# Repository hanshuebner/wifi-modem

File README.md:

# WiFi modem based on Zimodem

This project contains a PCB to turn a ESP-12F microcontroller into a
standalone WiFi modem with status LEDs and a RS-232 interface.  It is
designed to use [Zimodem](https://github.com/bozimmerman/Zimodem) as
firmware.

**Please do not use this PCB at this points.  There are bugs in it that
make it non-functional and I did not find the time to debug it yet.**

[schematics](schematic.pdf)

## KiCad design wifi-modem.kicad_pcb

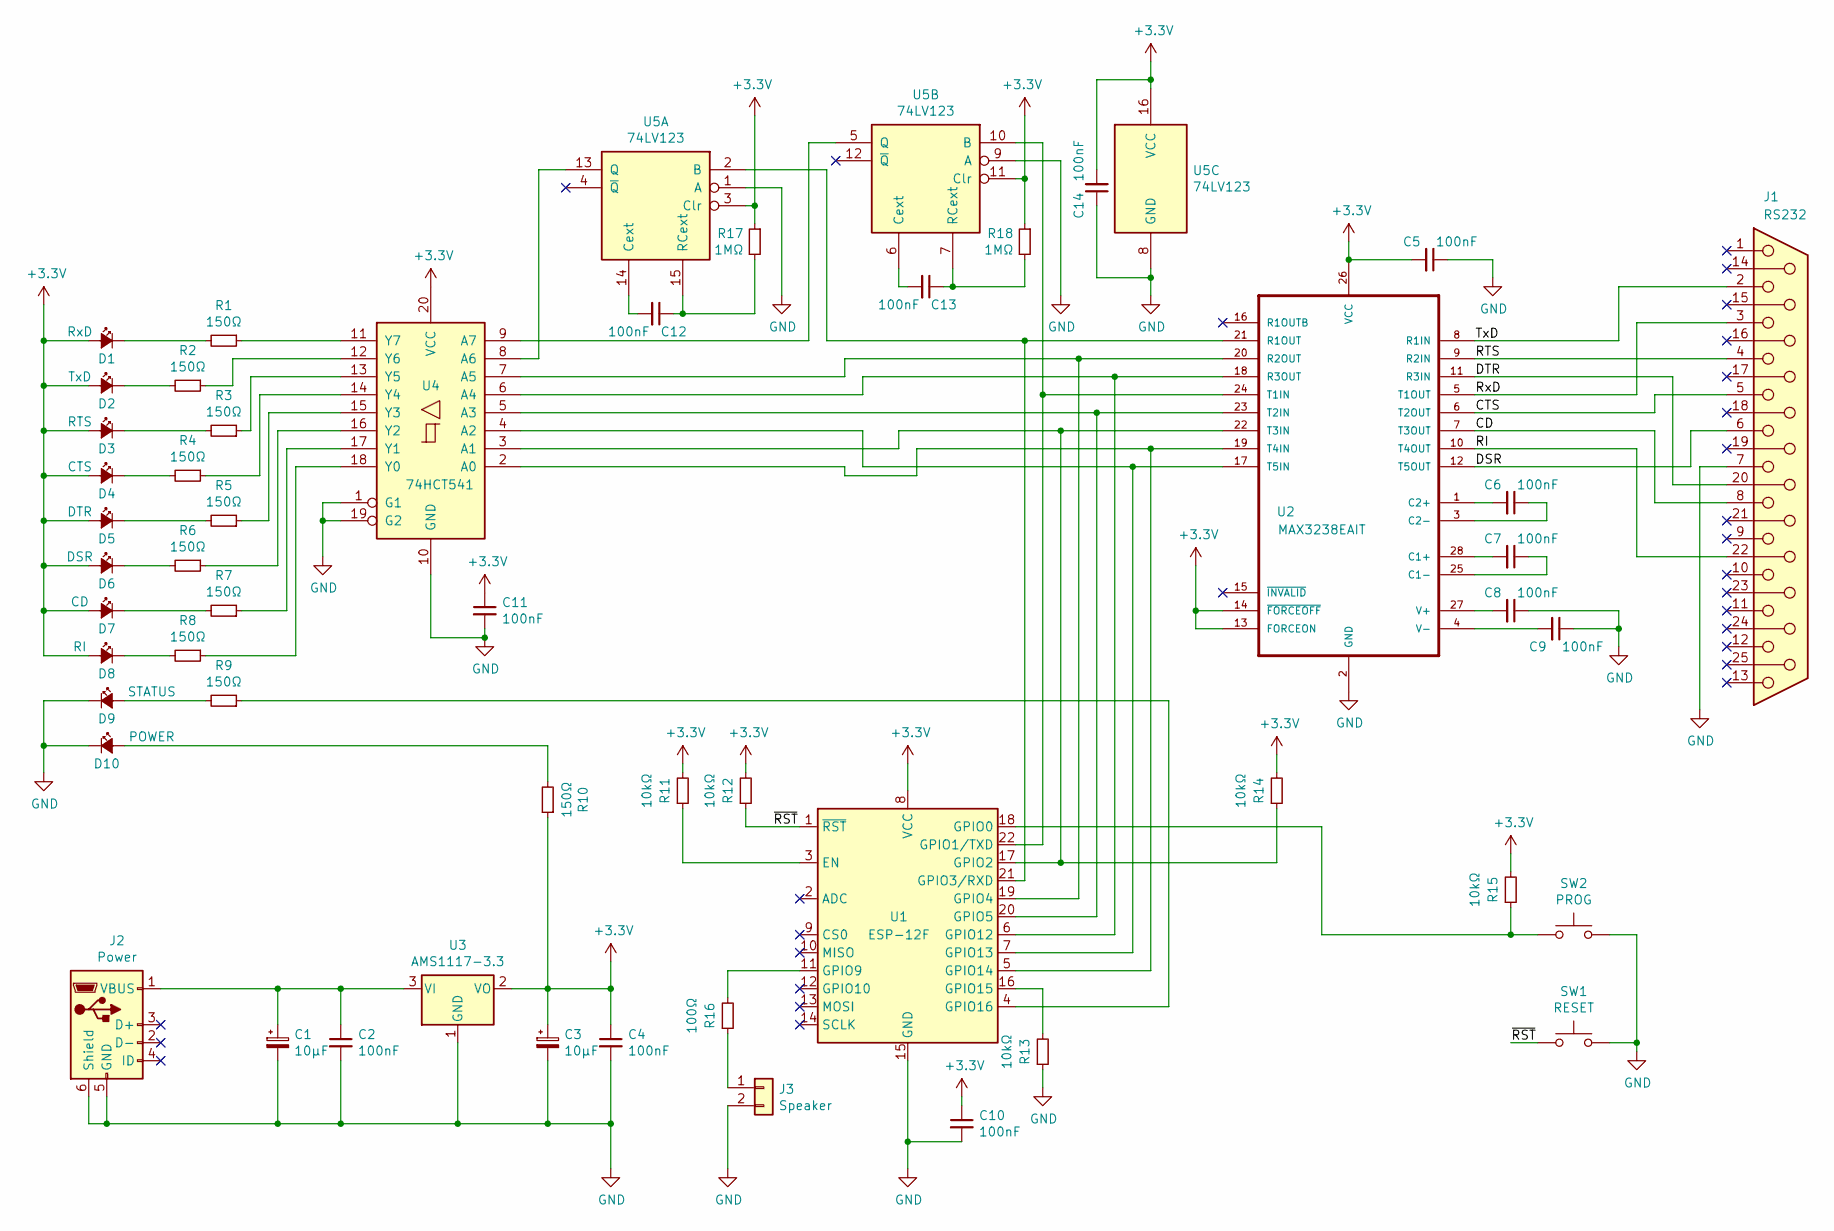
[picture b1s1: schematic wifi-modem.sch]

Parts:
C1, C3: 10µF; C_0805_2012Metric_Pad1.15x1.40mm_HandSolder
C2, C4, C5, C6, C7, C8, C9, C10, C11, C12, C13, C14: 100nF; C_0805_2012Metric_Pad1.15x1.40mm_HandSolder
D1: RxD; LED_D5.0mm
D2: TxD; LED_D5.0mm
D3: RTS; LED_D5.0mm
D4: CTS; LED_D5.0mm
D5: DTR; LED_D5.0mm
D6: DSR; LED_D5.0mm
D7: CD; LED_D5.0mm
D8: RI; LED_D5.0mm
D9: STATUS; LED_D5.0mm
D10: POWER; LED_D5.0mm
J1: RS232; DSUB-25_Female_Horizontal_P2.77x2.84mm_EdgePinOffset7.70mm_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
J2: Power; USB_Micro-B_Wuerth_629105150521
J3: Speaker; PinHeader_1x02_P2.54mm_Vertical
R1, R2, R3, R4, R5, R6, R7, R8, R9, R10: 150Ω; R_0805_2012Metric_Pad1.15x1.40mm_HandSolder
R11, R12, R13, R14, R15: 10kΩ; R_0805_2012Metric_Pad1.15x1.40mm_HandSolder
R16: 100Ω; R_0805_2012Metric_Pad1.15x1.40mm_HandSolder
R17, R18: 1MΩ; R_0805_2012Metric_Pad1.15x1.40mm_HandSolder
SW1: RESET; SW_Push_1P1T_NO_6x6mm_H9.5mm
SW2: PROG; SW_Push_1P1T_NO_6x6mm_H9.5mm
U1: ESP-12F; ESP-12E
U2: MAX3238EAIT; SOP65P777X199-28N
U3: AMS1117-3.3; SOT-223-3_TabPin2
U4: 74HCT541; TSSOP-20_4.4x6.5mm_P0.65mm
U5: 74LV123; TSSOP-16_4.4x5mm_P0.65mm

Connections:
+3V3: C3.1, C4.1, C5.2, C10.1, C11.1, C14.2, D1.2 (A), D2.2 (A), D3.2 (A), D4.2 (A), D5.2 (A), D6.2 (A), D7.2 (A), D8.2 (A), R10.1, R11.2, R12.2, R14.2, R15.2, R17.1, R18.1, U1.8 (VCC), U2.13 (FORCEON), U2.14 (~FORCEOFF~), U2.26 (VCC), U3.2 (VO), U4.20 (VCC), U5.3 (Clr), U5.11 (Clr), U5.16 (VCC)
/CD: J1.8, U2.7 (T3OUT)
/CTS: J1.5, U2.6 (T2OUT)
/DSR: J1.6, U2.12 (T5OUT)
/DTR: J1.20, U2.11 (R3IN)
/RI: J1.22, U2.10 (T4OUT)
/RTS: J1.4, U2.9 (R2IN)
/RxD: J1.3, U2.5 (T1OUT)
/TxD: J1.2, U2.8 (R1IN)
/~RST: R12.1, SW1.1, U1.1 (~RST)
GND: C1.2, C2.2, C3.2, C4.2, C5.1, C8.1, C9.1, C10.2, C11.2, C14.1, D9.1 (K), D10.1 (K), J1.7, J2.5 (GND), J2.6 (Shield), J3.2, R13.1, SW1.2, SW2.2, U1.15 (GND), U2.2 (GND), U3.1 (GND), U4.1 (G1), U4.10 (GND), U4.19 (G2), U5.1 (A), U5.8 (GND), U5.9 (A)
unnamed: C1.1, C2.1, J2.1 (VBUS), U3.3 (VI)
unnamed: C6.1, U2.3 (C2-)
unnamed: C6.2, U2.1 (C2+)
unnamed: C7.1, U2.25 (C1-)
unnamed: C7.2, U2.28 (C1+)
unnamed: C8.2, U2.27 (V+)
unnamed: C9.2, U2.4 (V-)
unnamed: C12.1, R17.2, U5.15 (RCext)
unnamed: C12.2, U5.14 (Cext)
unnamed: C13.1, R18.2, U5.7 (RCext)
unnamed: C13.2, U5.6 (Cext)
unnamed: D1.1 (K), R1.2
unnamed: D2.1 (K), R2.2
unnamed: D3.1 (K), R3.2
unnamed: D4.1 (K), R4.2
unnamed: D5.1 (K), R5.2
unnamed: D6.1 (K), R6.2
unnamed: D7.1 (K), R7.2
unnamed: D8.1 (K), R8.2
unnamed: D9.2 (A), R9.2
unnamed: D10.2 (A), R10.2
unnamed: J3.1, R16.1
unnamed: R1.1, U4.11 (Y7)
unnamed: R2.1, U4.12 (Y6)
unnamed: R3.1, U4.13 (Y5)
unnamed: R4.1, U4.14 (Y4)
unnamed: R5.1, U4.15 (Y3)
unnamed: R6.1, U4.16 (Y2)
unnamed: R7.1, U4.17 (Y1)
unnamed: R8.1, U4.18 (Y0)
unnamed: R9.1, U1.4 (GPIO16)
unnamed: R11.1, U1.3 (EN)
unnamed: R13.2, U1.16 (GPIO15)
unnamed: R14.1, U1.17 (GPIO2), U2.22 (T3IN), U4.3 (A1)
unnamed: R15.1, SW2.1, U1.18 (GPIO0)
unnamed: R16.2, U1.11 (GPIO9)
unnamed: U1.5 (GPIO14), U2.19 (T4IN), U4.2 (A0)
unnamed: U1.6 (GPIO12), U2.18 (R3OUT), U4.6 (A4)
unnamed: U1.7 (GPIO13), U2.17 (T5IN), U4.4 (A2)
unnamed: U1.19 (GPIO4), U2.20 (R2OUT), U4.7 (A5)
unnamed: U1.20 (GPIO5), U2.23 (T2IN), U4.5 (A3)
unnamed: U1.21 (GPIO3/RXD), U2.21 (R1OUT), U5.2 (B)
unnamed: U1.22 (GPIO1/TXD), U2.24 (T1IN), U5.10 (B)
unnamed: U4.8 (A6), U5.13 (Q)
unnamed: U4.9 (A7), U5.5 (Q)

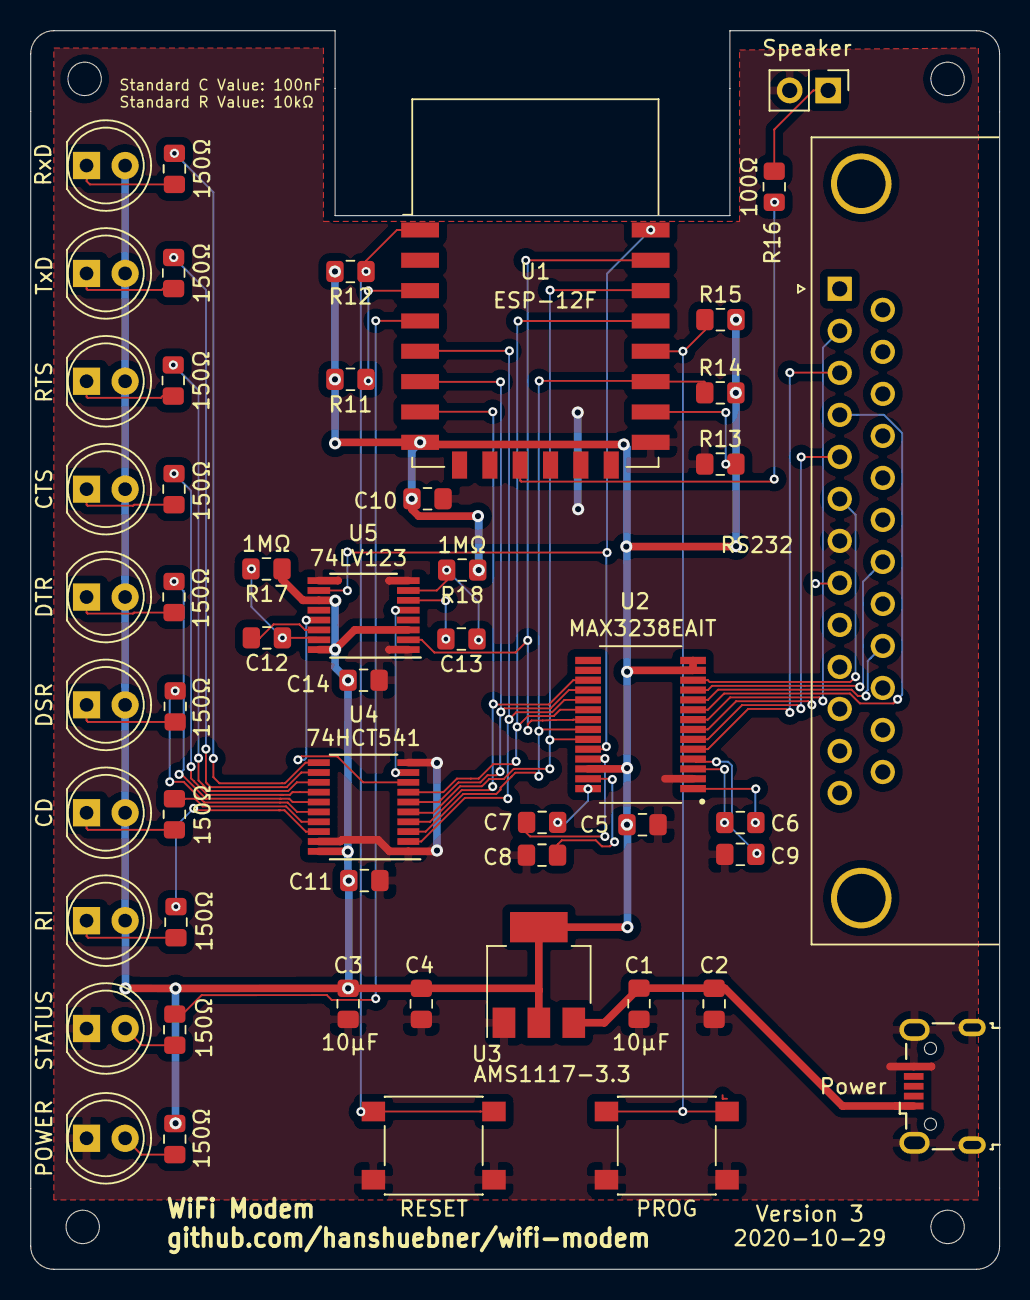
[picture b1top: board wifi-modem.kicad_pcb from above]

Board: 2 copper layers, 63.9 x 81.7 mm, 52 parts (0 on the bottom side), 56 nets.

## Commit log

2020-08-28 Snapshot
2020-08-28 Checkpoint
2020-08-28 Layout redone
2020-08-28 Fixed connectors, added Speaker, made larger
2020-08-28 Fix swapped RX/TX lines
2020-08-28 V1 sent to JLCPCB
2020-08-28 Sent to JLCPCB
2020-08-28 README and image/PDF
2020-08-28 tweaks
2020-10-04 Added LED drivers
2020-10-30 PCB Version 3
